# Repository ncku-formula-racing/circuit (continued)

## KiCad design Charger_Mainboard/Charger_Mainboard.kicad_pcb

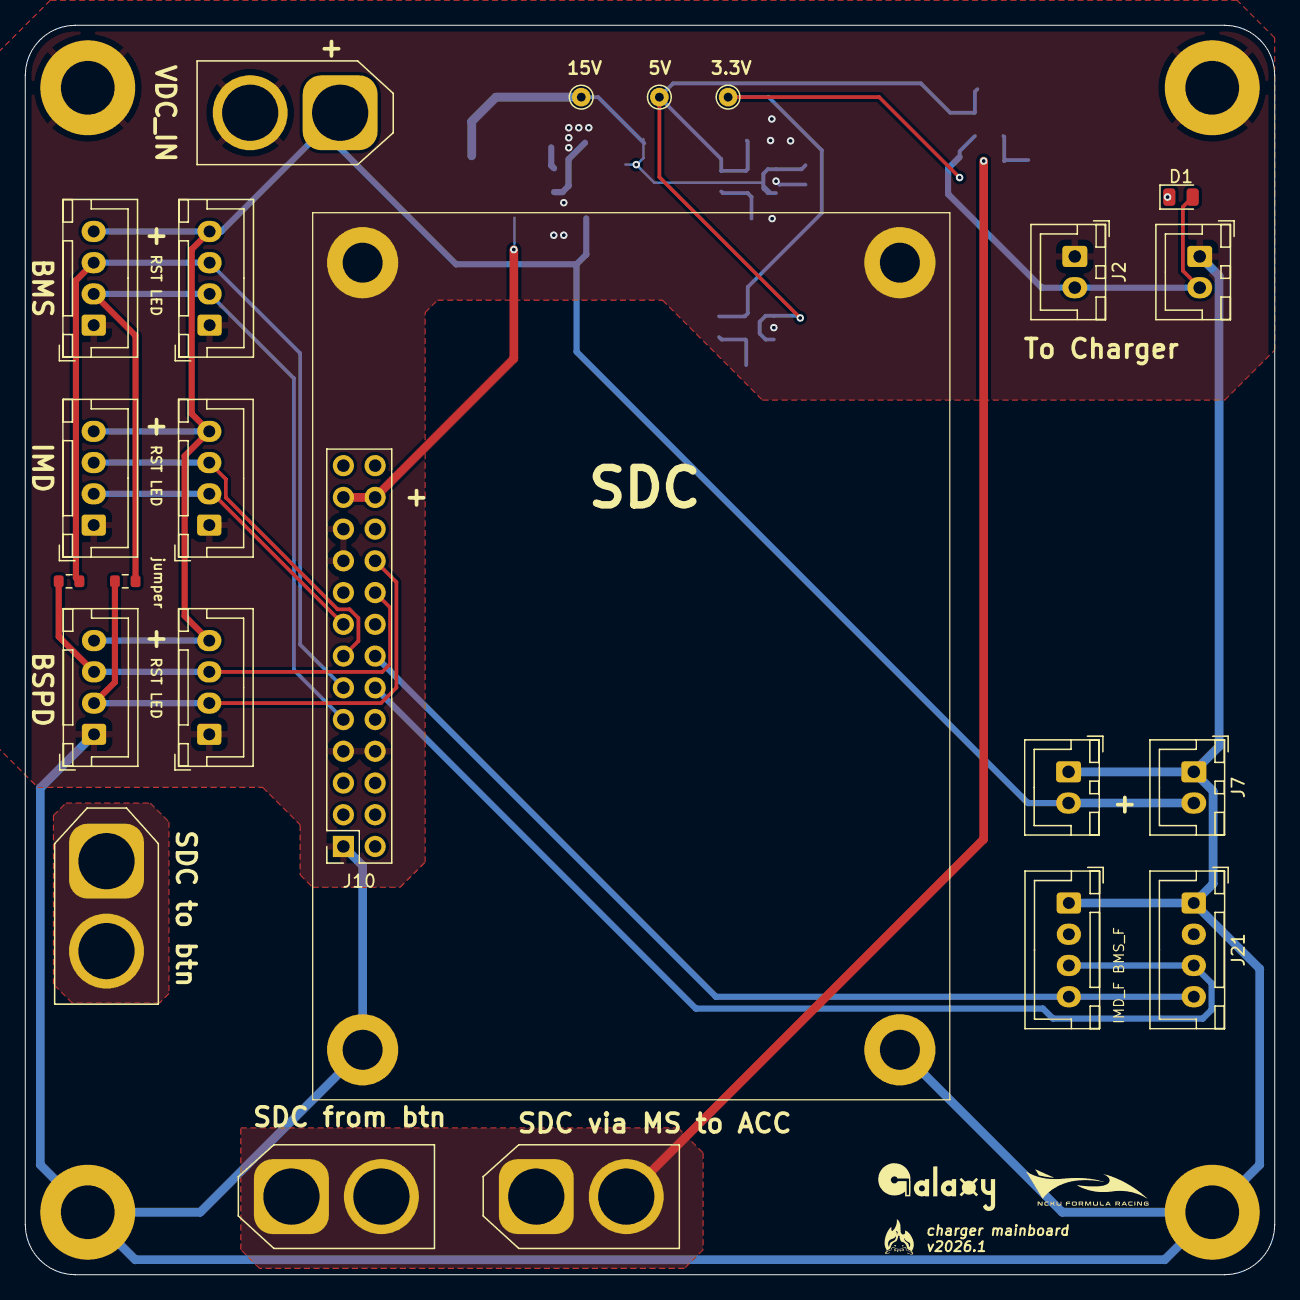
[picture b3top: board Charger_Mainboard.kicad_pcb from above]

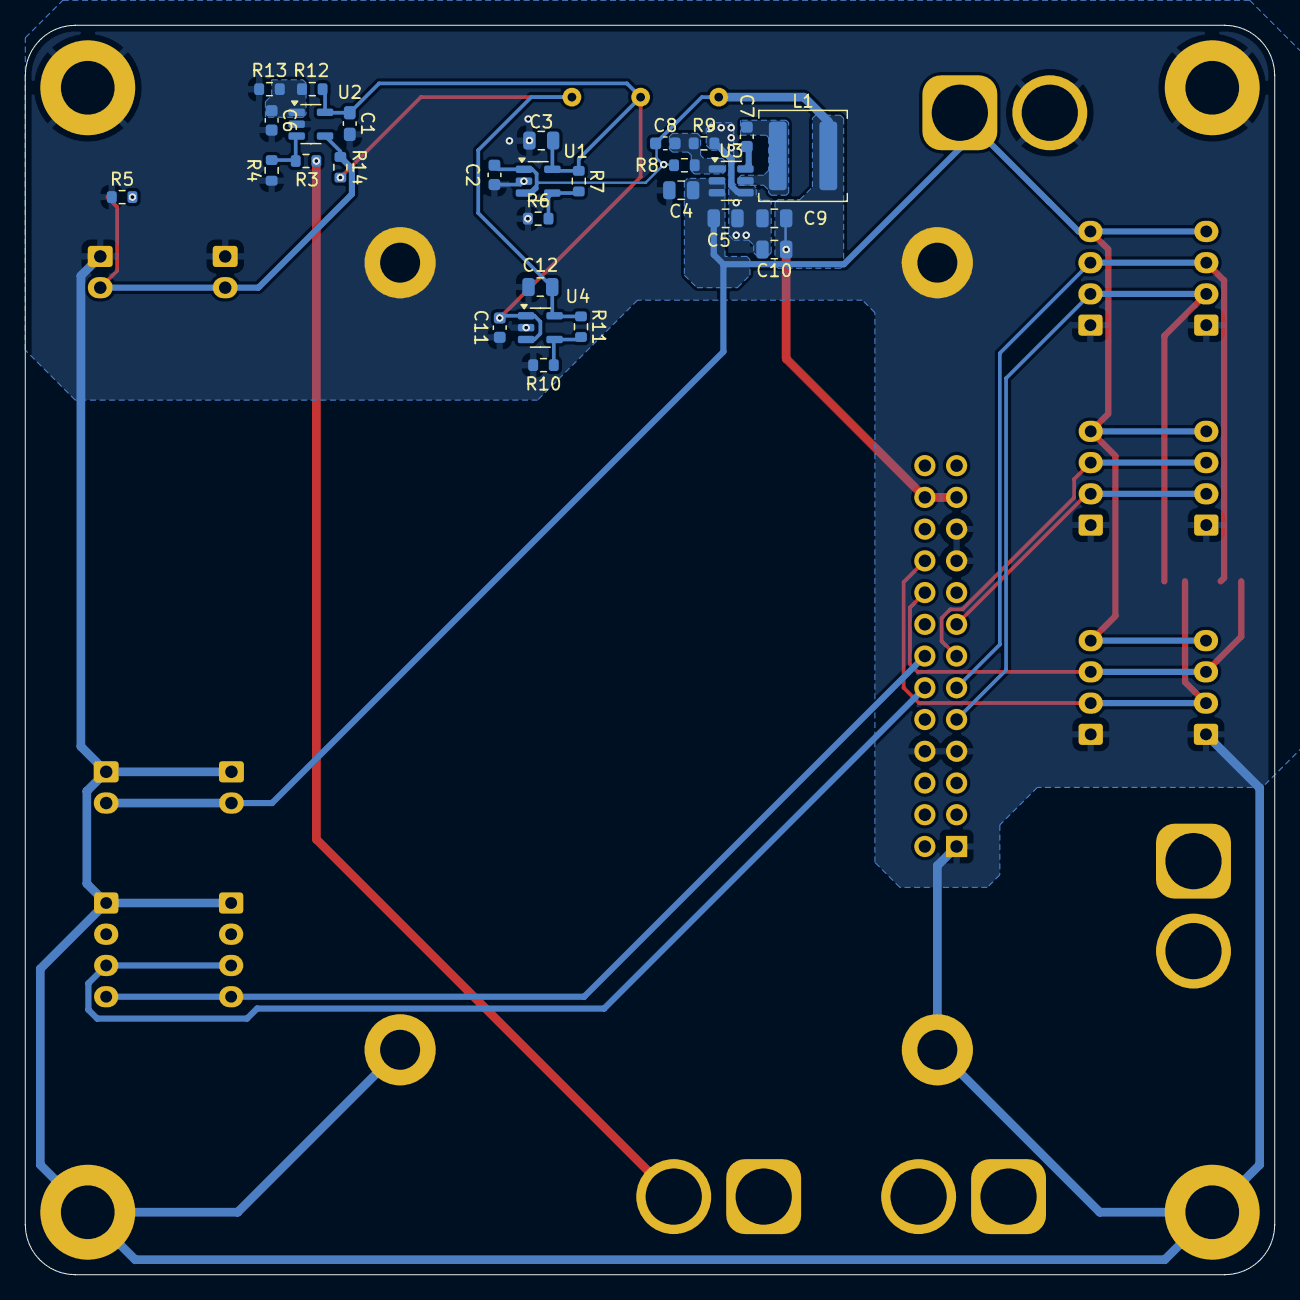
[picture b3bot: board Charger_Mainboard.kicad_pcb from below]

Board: 2 copper layers, 100.0 x 100.0 mm, 60 parts (29 on the bottom side), 24 nets.

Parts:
C1: 1u; C_0603_1608Metric_Pad1.08x0.95mm_HandSolder
C2, C11: 1u; C_0603_1608Metric
C3, C4, C5, C12: 10u; C_0805_2012Metric
C6, C7: 100n; C_0603_1608Metric
C8: 12p; C_0603_1608Metric
C9, C10: 22u; C_0805_2012Metric
D1: LED_Small; LED_0805_2012Metric
H1, H2#2, H3, H4#2: MountingHole_Pad; MountingHole_4.3mm_M4_ISO7380_Pad
H1#2, H2, H3#2, H4: MountingHole_Pad; MountingHole_3.2mm_M3_ISO7380_Pad
J1, J3, J4, J5: Conn_01x02; AMASS_XT60-M_1x02_P7.20mm_Vertical
J2, J2#2, J7, J7#2: Conn_01x02; JST_XH_B2B-XH-A_1x02_P2.50mm_Vertical
J8, J8#2, J18, J18#2, J21, J21#2, J22, J22#2: Conn_01x04; JST_XH_B4B-XH-A_1x04_P2.50mm_Vertical
J10: Conn_02x13_Odd_Even; PinSocket_2x13_P2.54mm_Vertical
L1: 15uH; L_Coilcraft_XAL6060-XXX
R1, R2: 0; R_0603_1608Metric
R3, R7: 301k; R_0603_1608Metric
R4, R6, R10: 100k; R_0603_1608Metric
R5, R12, R13: 10k; R_0603_1608Metric
R8: 534k; R_0603_1608Metric
R9: 30k1; R_0603_1608Metric
R11: 165k; R_0603_1608Metric
R14: 1k; R_0603_1608Metric
TP1, TP2, TP3: TestPoint; TestPoint_THTPad_D1.5mm_Drill0.7mm
U1, U4: AP2204K-ADJ; SOT-23-5
U2: AS331KTR-G1; SOT-23-5
U3: AP63200WU; TSOT-23-6

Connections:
+3V3: C12.1, R11.1, R14.1, TP3.1, U4.5 (VOUT)
+5V: C1.1, C3.1, C11.1, R7.1, R12.1, TP2.1, U1.5 (VOUT), U2.5, U4.1 (VIN), U4.3 (EN)
BMS_FAULT: J10.12, J21.3, J21#2.3
BMS_LED: J10.9, J22.2, J22#2.2, R2.1
BMS_RST: J10.11, J22.3, J22#2.3, R1.2
BSPD_LED: J8.2, J8#2.2, J10.20, R2.2
BSPD_RST: J8.3, J8#2.3, J10.18, R1.1
GND: C1.2, C2.2, C3.2, C4.2, C5.2, C6.2, C9.2, C10.2, C11.2, C12.2, H1.1, H1#2.1, H2.1, H2#2.1, H3.1, H3#2.1, H4.1, H4#2.1, J1.2, J2.1, J2#2.1, J7.1, J7#2.1, J8.1, J8#2.1, J10.1, J10.7, J10.8, J10.19, J10.21, J18.1, J18#2.1, J21.1, J21#2.1, J22.1, J22#2.1, R4.1, R5.1, R6.1, R9.2, R10.1, R13.2, U1.2 (GND), U2.2, U3.4 (GND), U4.2 (GND)
IMD_FAULT: J10.14, J21.4, J21#2.4
IMD_LED: J10.15, J18.2, J18#2.2
IMD_RST: J10.13, J18.3, J18#2.3
unnamed: D1.1 (K), R5.2
unnamed: R6.2, R7.2, U1.4 (ADJ)
unnamed: R3.1, R4.2, U2.3 (+)
unnamed: C6.1, R12.2, R13.1, U2.1 (-)
unnamed: C7.2, U3.6 (BST)
unnamed: C8.2, R8.2, R9.1, U3.1 (FB)
unnamed: C7.1, L1.1, U3.5 (SW)
unnamed: R10.2, R11.2, U4.4 (ADJ)
SDC_FROM_SDBUTTON: J4.1, J4.2, J5.1, J5.2, R3.2
SDC_IN: C2.1, C8.1, C9.1, C10.1, J10.23, J10.24, L1.2, R8.1, TP1.1, U1.1 (VIN), U1.3 (EN)
SDC_TO_SDBUTTON: J3.1, J3.2
VDC: C4.1, C5.1, J1.1, J7.2, J7#2.2, J8.4, J8#2.4, J18.4, J18#2.4, J22.4, J22#2.4, U3.2 (EN), U3.3 (IN)
charger_analog: D1.2 (A), J2.2, J2#2.2, R14.2, U2.4

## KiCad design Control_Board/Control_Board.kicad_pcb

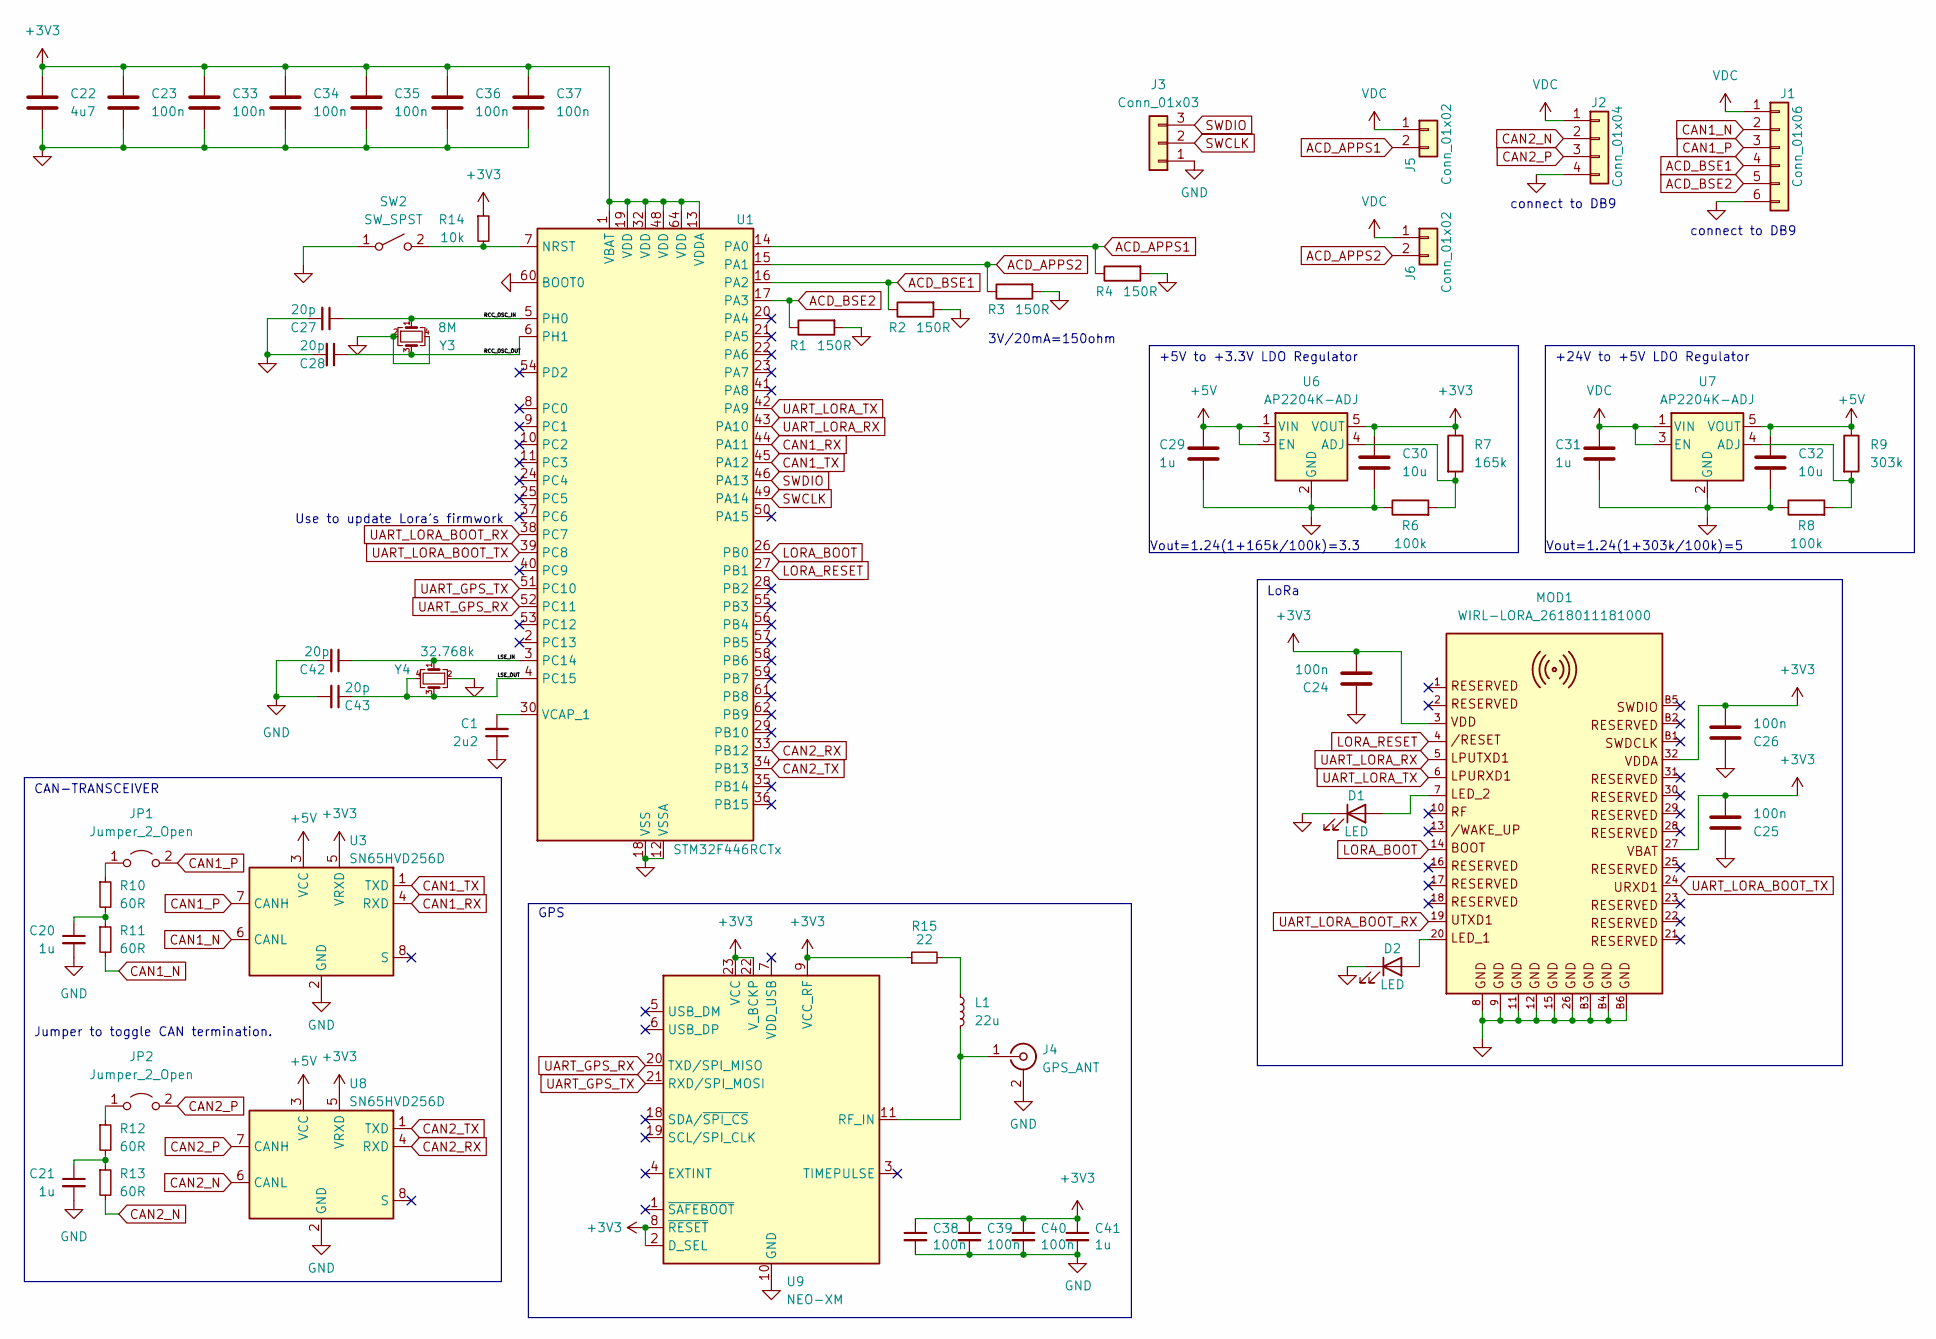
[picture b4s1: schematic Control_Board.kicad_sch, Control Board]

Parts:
C1: 2u2; C_0805_2012Metric
C20, C21, C29, C31, C41: 1u; C_0603_1608Metric
C22: 4u7; C_0805_2012Metric
C23, C24, C25, C26, C33, C34, C35, C36, C37, C38, C39, C40: 100n; C_0603_1608Metric
C27, C28, C42, C43: 20p; C_0603_1608Metric
C30, C32: 10u; C_0805_2012Metric
D1, D2: LED; LED_0805_2012Metric
J1: Conn_01x06; JST_XH_B6B-XH-A_1x06_P2.50mm_Vertical
J2: Conn_01x04; JST_XH_B4B-XH-A_1x04_P2.50mm_Vertical
J3: Conn_01x03; PinHeader_1x03_P2.54mm_Vertical
J4: GPS_ANT; U.FL_Hirose_U.FL-R-SMT-1_Vertical
J5, J6: Conn_01x02; JST_XH_B2B-XH-A_1x02_P2.50mm_Vertical
JP1, JP2: Jumper_2_Open; Jumper_P2.54mm_D0.7mm
L1: 22u; L_0805_2012Metric
MOD1: WIRL-LORA_2618011181000; WE-FP-8
R1, R2, R3, R4: 150R; R_0603_1608Metric
R6, R8: 100k; R_0603_1608Metric
R7: 165k; R_0603_1608Metric
R9: 303k; R_0603_1608Metric
R10, R11, R12, R13: 60R; R_0603_1608Metric
R14: 10k; R_0603_1608Metric
R15: 22; R_0603_1608Metric
SW2: SW_SPST; SW_SPST_FSMSM
U1: STM32F446RCTx; LQFP-64_10x10mm_P0.5mm
U3, U8: SN65HVD256D; SOIC-8_3.9x4.9mm_P1.27mm
U6, U7: AP2204K-ADJ; SOT-23-5
U9: NEO-XM; ublox_NEO
Y3: 8M; Crystal_SMD_SeikoEpson_FA238-4Pin_3.2x2.5mm
Y4: 32.768k; Crystal_SMD_SeikoEpson_FA238-4Pin_3.2x2.5mm

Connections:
+3V3: C22.1, C23.1, C24.2, C25.2, C26.2, C30.1, C33.1, C34.1, C35.1, C36.1, C37.1, C38.1, C39.1, C40.1, C41.1, MOD1.3, MOD1.27, MOD1.32, R7.1, R14.1, R15.1, U1.1 (VBAT), U1.13 (VDDA), U1.19 (VDD), U1.32 (VDD), U1.48 (VDD), U1.64 (VDD), U3.5 (VRXD), U6.5 (VOUT), U8.5 (VRXD), U9.2 (D_SEL), U9.8 (~RESET), U9.9 (VCC_RF), U9.22 (V_BCKP), U9.23 (VCC)
+5V: C29.1, C32.1, R9.1, U3.3 (VCC), U6.1 (VIN), U6.3 (EN), U7.5 (VOUT), U8.3 (VCC)
/LSE_IN: C42.1, U1.3 (PC14), Y4.1
/LSE_OUT: C43.1, U1.4 (PC15), Y4.3, Y4.4
/RCC_OSC_IN: C27.1, U1.5 (PH0), Y3.1
/RCC_OSC_OUT: C28.1, U1.6 (PH1), Y3.3
ACD_APPS1: J5.2, R4.1, U1.14 (PA0)
ACD_APPS2: J6.2, R3.1, U1.15 (PA1)
ACD_BSE1: J1.4, R2.1, U1.16 (PA2)
ACD_BSE2: J1.5, R1.1, U1.17 (PA3)
CAN1_N: J1.2, R11.2, U3.6 (CANL)
CAN1_P: J1.3, JP1.2 (B), U3.7 (CANH)
CAN1_RX: U1.44 (PA11), U3.4 (RXD)
CAN1_TX: U1.45 (PA12), U3.1 (TXD)
CAN2_N: J2.2, R13.2, U8.6 (CANL)
CAN2_P: J2.3, JP2.2 (B), U8.7 (CANH)
CAN2_RX: U1.33 (PB12), U8.4 (RXD)
CAN2_TX: U1.34 (PB13), U8.1 (TXD)
GND: C1.1, C20.2, C21.2, C22.2, C23.2, C24.1, C25.1, C26.1, C27.2, C28.2, C29.2, C30.2, C31.2, C32.2, C33.2, C34.2, C35.2, C36.2, C37.2, C38.2, C39.2, C40.2, C41.2, C42.2, C43.2, D1.1 (K), D2.1 (K), J1.6, J2.4, J3.1, J4.2 (Ext), MOD1.8, MOD1.9, MOD1.11, MOD1.12, MOD1.15, MOD1.26, MOD1.B3, MOD1.B4, MOD1.B6, R1.2, R2.2, R3.2, R4.2, R6.1, R8.1, SW2.1 (A), U1.12 (VSSA), U1.18 (VSS), U1.31 (VSS), U1.47 (VSS), U1.60 (BOOT0), U1.63 (VSS), U3.2 (GND), U6.2 (GND), U7.2 (GND), U8.2 (GND), U9.10 (GND), U9.12 (GND), U9.13 (GND), U9.24 (GND), Y3.2, Y3.4, Y4.2
LORA_BOOT: MOD1.14, U1.26 (PB0)
LORA_RESET: MOD1.4, U1.27 (PB1)
unnamed: C20.1, R10.2, R11.1
unnamed: C21.1, R12.2, R13.1
unnamed: D1.2 (A), MOD1.7
unnamed: D2.2 (A), MOD1.20
unnamed: J4.1 (In), L1.2, U9.11 (RF_IN)
unnamed: JP1.1 (A), R10.1
unnamed: JP2.1 (A), R12.1
unnamed: L1.1, R15.2
unnamed: R14.2, SW2.2 (B), U1.7 (NRST)
unnamed: C1.2, U1.30 (VCAP_1)
unnamed: R6.2, R7.2, U6.4 (ADJ)
unnamed: R8.2, R9.2, U7.4 (ADJ)
SWCLK: J3.2, U1.49 (PA14)
SWDIO: J3.3, U1.46 (PA13)
UART_GPS_RX: U1.52 (PC11), U9.20 (TXD/SPI_MISO)
UART_GPS_TX: U1.51 (PC10), U9.21 (RXD/SPI_MOSI)
UART_LORA_BOOT_RX: MOD1.19, U1.38 (PC7)
UART_LORA_BOOT_TX: MOD1.24, U1.39 (PC8)
UART_LORA_RX: MOD1.5, U1.43 (PA10)
UART_LORA_TX: MOD1.6, U1.42 (PA9)
VDC: C31.1, J1.1, J2.1, J5.1, J6.1, U7.1 (VIN), U7.3 (EN)

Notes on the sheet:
Vout=1.24(1+165k/100k)=3.3
connect to DB9
Jumper to toggle CAN termination.
CAN-TRANSCEIVER
Vout=1.24(1+303k/100k)=5
3V/20mA=150ohm
GPS
Use to update Lora's firmwork
+24V to +5V LDO Regulator
+5V to +3.3V LDO Regulator
LoRa

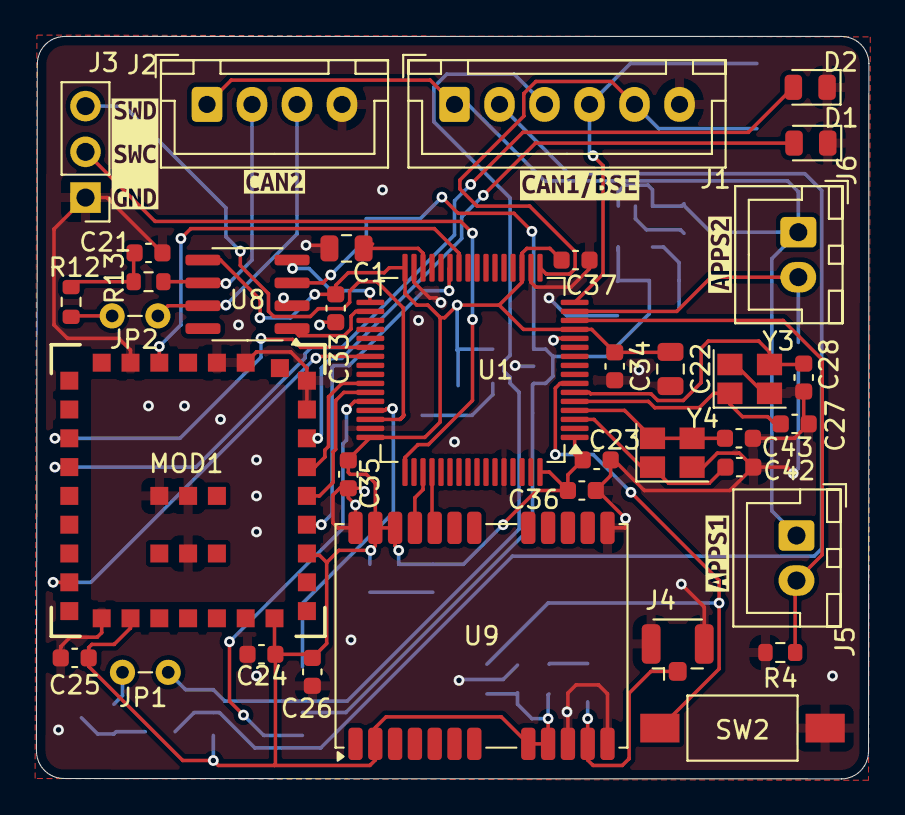
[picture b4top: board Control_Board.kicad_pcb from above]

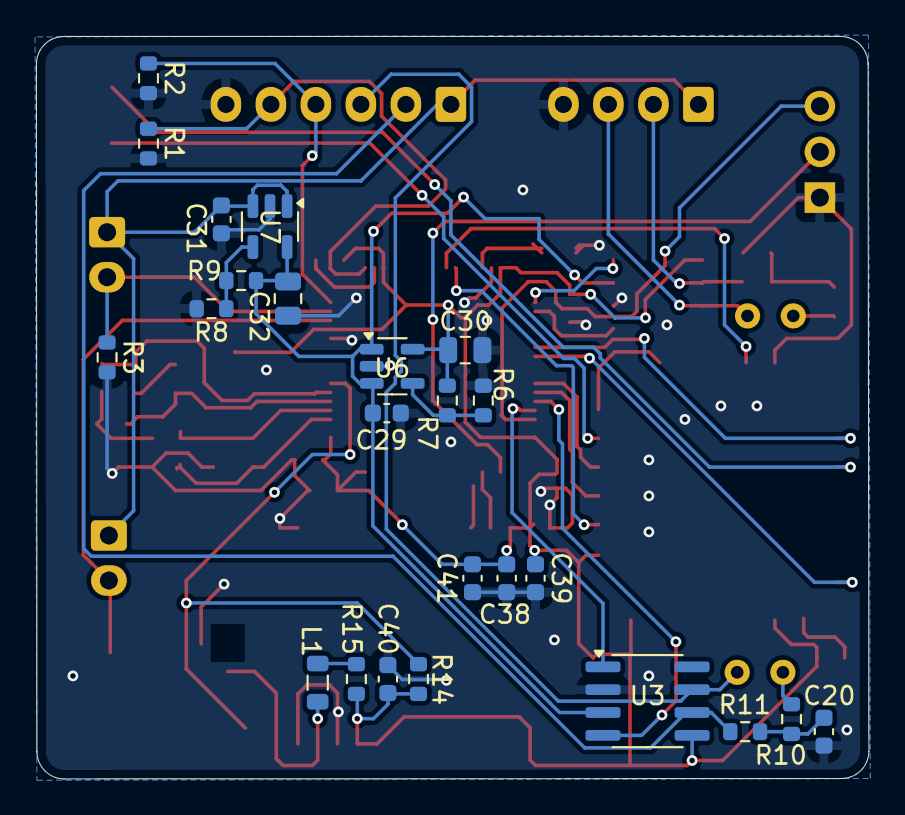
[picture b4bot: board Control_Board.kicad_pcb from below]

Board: 2 copper layers, 46.3 x 41.3 mm, 65 parts (24 on the bottom side), 42 nets.

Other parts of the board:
kibuzzard-68852EE2: G***; kibuzzard-68852EE2
kibuzzard-68852F9B: G***; kibuzzard-68852F9B
kibuzzard-68852FF1: G***; kibuzzard-68852FF1
kibuzzard-68853119: G***; kibuzzard-68853119
kibuzzard-68853151: G***; kibuzzard-68853151

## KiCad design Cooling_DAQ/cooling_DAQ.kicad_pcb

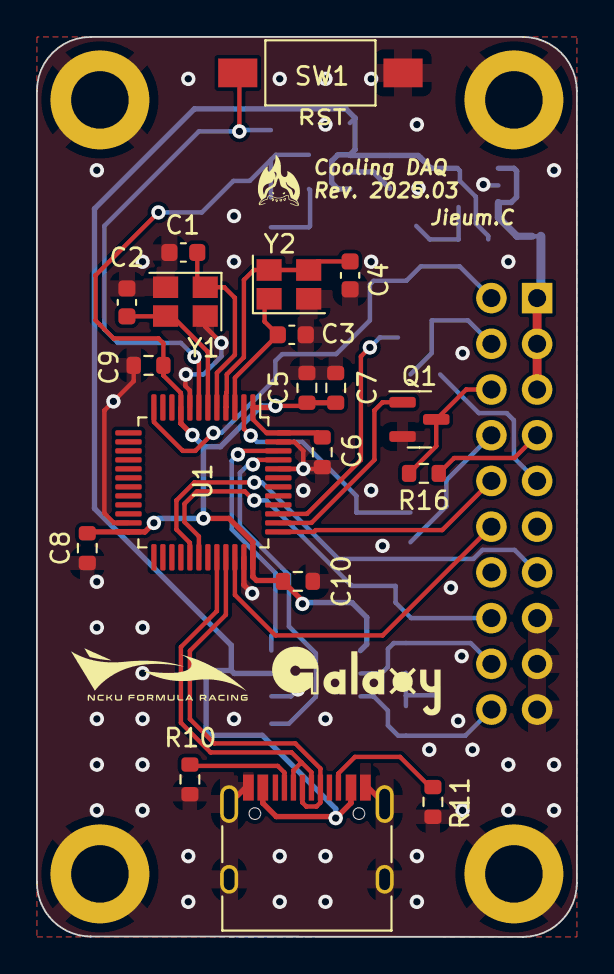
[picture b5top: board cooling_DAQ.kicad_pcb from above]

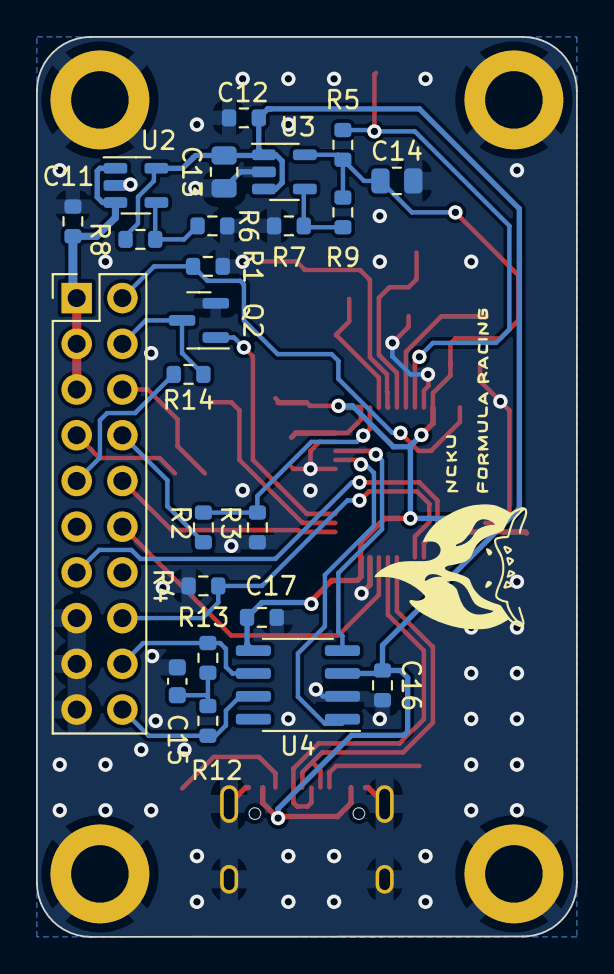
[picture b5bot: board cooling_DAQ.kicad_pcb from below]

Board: 2 copper layers, 30.0 x 50.0 mm, 47 parts (24 on the bottom side), 33 nets.

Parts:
C1, C2, C3, C4: 20p; C_0603_1608Metric
C5, C6, C8, C9, C10, C16, C17: 100n; R_0603_1608Metric
C7, C11, C12: 1u; R_0603_1608Metric
C13, C14: 10u; R_0805_2012Metric
C15: 1u; C_0603_1608Metric
H1, H2, H3, H4: MountingHole_Pad; MountingHole_3.2mm_M3_ISO14580_Pad
J1: Conn_02x10_Odd_Even; PinHeader_2x10_P2.54mm_Vertical
J7: USB_C_Receptacle_USB2.0_16P; USB_C_Receptacle_HRO_TYPE-C-31-M-12
Q1, Q2: 2N7002; SOT-23
R1, R4: 4.7k; R_0603_1608Metric
R2: 47k; R_0603_1608Metric
R3, R6, R7: 100k; R_0603_1608Metric
R5, R14, R16: 10k; R_0603_1608Metric
R8: 301k; R_0603_1608Metric
R9: 165k; R_0603_1608Metric
R10, R11: 5k1; R_0603_1608Metric
R12, R13: 60R; R_0603_1608Metric
SW1: SW_SPST; SW_SPST_FSMSM
U1: STM32F103C8Tx; LQFP-48_7x7mm_P0.5mm
U2, U3: AP2204K-ADJ; SOT-23-5
U4: SN65HVD256D; SOIC-8_3.9x4.9mm_P1.27mm
Y1: 8M; Crystal_SMD_SeikoEpson_FA238-4Pin_3.2x2.5mm
Y2: 32.768k; Crystal_SMD_SeikoEpson_FA238-4Pin_3.2x2.5mm

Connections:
+3V3: C5.1, C6.1, C7.1, C8.1, C9.1, C10.1, C14.1, C17.1, R5.1, R9.1, U1.1 (VBAT), U1.9 (VDDA), U1.24 (VDD), U1.36 (VDD), U1.48 (VDD), U3.5 (VOUT), U4.5 (VRXD)
+5V: C12.1, C13.1, C16.1, J7.A4 (VBUS), J7.A9 (VBUS), J7.B4 (VBUS), J7.B9 (VBUS), R8.1, U2.5 (VOUT), U3.1 (VIN), U3.3 (EN), U4.3 (VCC)
/LSE_IN: C3.1, U1.3 (PC14), Y2.1
/LSE_OUT: C4.1, U1.4 (PC15), Y2.3, Y2.4
/RCC_OSC_IN: C1.1, U1.5 (PD0), Y1.1
/RCC_OSC_OUT: C2.1, U1.6 (PD1), Y1.3
ADC_CH1: R2.2, R3.1, U1.2 (PC13)
CAN+: J1.20, R12.1, U4.7 (CANH)
CAN-: J1.18, R13.2, U4.6 (CANL)
CAN_RX: U1.46 (PB9), U4.4 (RXD)
CAN_TX: U1.45 (PB8), U4.1 (TXD)
FAN_PWM: J1.4, Q2.3 (D), R14.1
FAN_PWR: J1.9, R14.2
GND: C1.2, C2.2, C3.2, C4.2, C5.2, C6.2, C7.2, C8.2, C9.2, C10.2, C11.2, C12.2, C13.2, C14.2, C15.2, C16.2, C17.2, H1.1, H2.1, H3.1, H4.1, J1.15, J1.17, J1.19, J7.A1 (GND), J7.A12 (GND), J7.B1 (GND), J7.B12 (GND), J7.S1 (SHIELD), Q1.2 (S), Q2.2 (S), R1.2, R3.2, R4.2, R6.1, R7.1, R10.2, R11.2, SW1.1 (A), U1.8 (VSSA), U1.23 (VSS), U1.35 (VSS), U1.44 (BOOT0), U1.47 (VSS), U2.2 (GND), U3.2 (GND), U4.2 (GND), Y1.2, Y1.4, Y2.2
unnamed: C15.1, R12.2, R13.1
unnamed: J7.A5 (CC1), R10.1
unnamed: J7.B5 (CC2), R11.1
unnamed: R5.2, SW1.2 (B), U1.7 (NRST)
unnamed: R6.2, R8.2, U2.4 (ADJ)
unnamed: R7.2, R9.2, U3.4 (ADJ)
PT_signal: J1.8, R2.1
PUMP_PWM: J1.6, Q1.3 (D), R16.1
PUMP_PWR: J1.7, R16.2
PWM_OUT: Q1.1 (G), U1.38 (PA15)
PWM_OUT_2: Q2.1 (G), U1.39 (PB3)
SYS_JTCK-SWCLK: J1.10, U1.37 (PA14)
SYS_JTMS-SWDIO: J1.12, U1.34 (PA13)
TIM1_CH1: J1.13, U1.29 (PA8)
USART1: J1.16, R4.1, U1.30 (PA9)
USART2: J1.2, R1.1, U1.12 (PA2)
USB_D+: J7.A6 (D+), J7.B6 (D+), U1.33 (PA12)
USB_D-: J7.A7 (D-), J7.B7 (D-), U1.32 (PA11)
VDC: C11.1, J1.1, J1.3, J1.5, U2.1 (VIN), U2.3 (EN)

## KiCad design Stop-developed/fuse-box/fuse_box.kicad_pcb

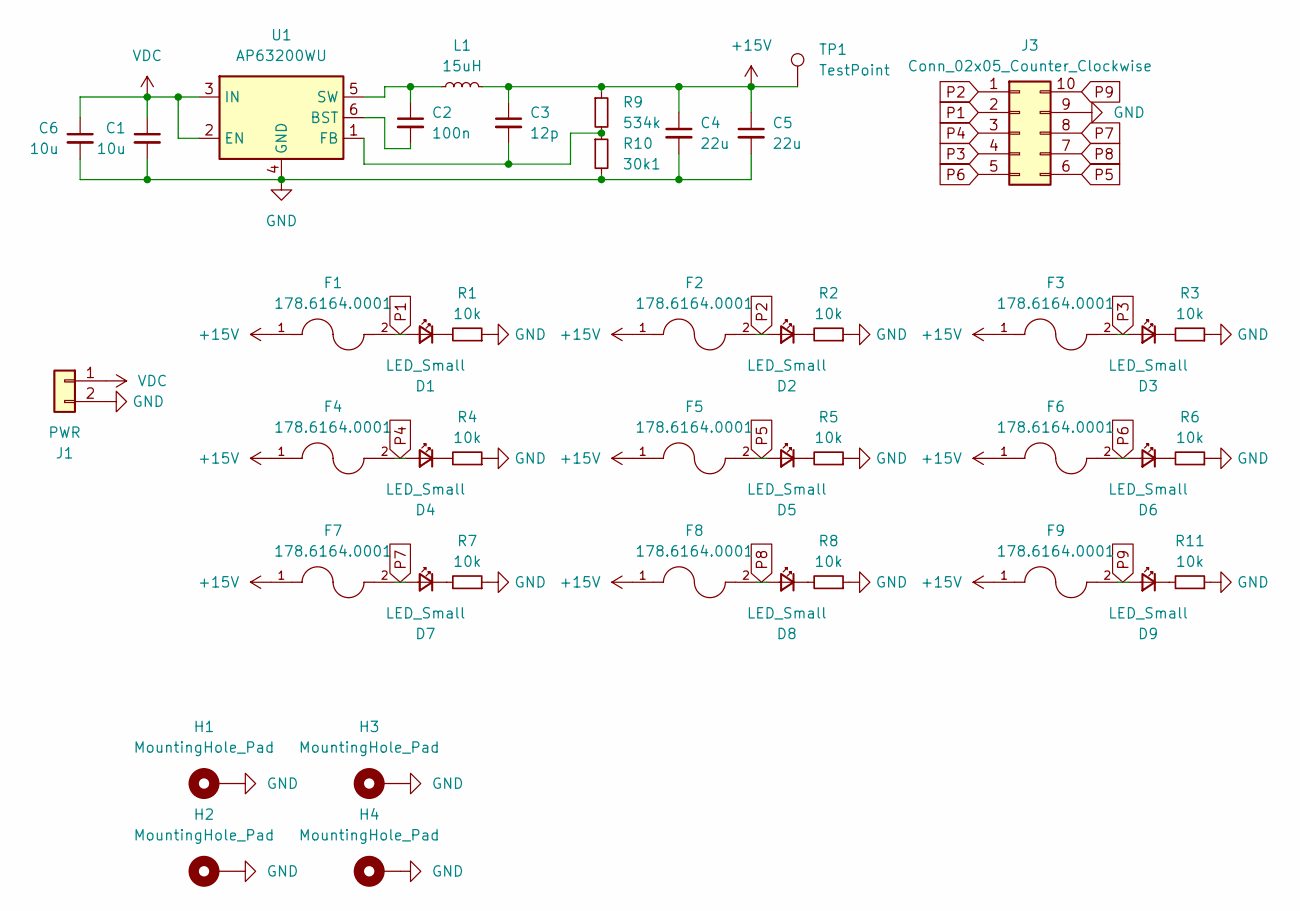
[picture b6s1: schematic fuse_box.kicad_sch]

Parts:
C1, C6: 10u; C_0805_2012Metric
C2: 100n; C_0603_1608Metric
C3: 12p; C_0603_1608Metric
C4, C5: 22u; C_0805_2012Metric
D1, D2, D3, D4, D5, D6, D7, D8, D9: LED_Small; LED_0805_2012Metric
F1, F2, F3, F4, F5, F6, F7, F8, F9: 178.6164.0001; LITTELFUSE_178.6164.0001; PARTREV 06.04.05
H1, H2, H3, H4: MountingHole_Pad; MountingHole_3.2mm_M3_ISO7380_Pad
J1: PWR; AMASS_XT60-M_1x02_P7.20mm_Vertical
J3: Conn_02x05_Counter_Clockwise; PinHeader_2x05_P2.54mm_Vertical
L1: 15uH; L_Coilcraft_XAL6060-XXX
R1, R2, R3, R4, R5, R6, R7, R8, R11: 10k; R_0603_1608Metric
R9: 534k; R_0603_1608Metric
R10: 30k1; R_0603_1608Metric
TP1: TestPoint; TestPoint_THTPad_D1.5mm_Drill0.7mm
U1: AP63200WU; TSOT-23-6

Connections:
+15V: C3.1, C4.1, C5.1, F1.1, F2.1, F3.1, F4.1, F5.1, F6.1, F7.1, F8.1, F9.1, L1.2, R9.1, TP1.1
GND: C1.2, C4.2, C5.2, C6.2, H1.1, H2.1, H3.1, H4.1, J1.2, J3.9, R1.1, R2.1, R3.1, R4.1, R5.1, R6.1, R7.1, R8.1, R10.2, R11.1, U1.4 (GND)
unnamed: D1.1 (K), R1.2
unnamed: D2.1 (K), R2.2
unnamed: D3.1 (K), R3.2
unnamed: D4.1 (K), R4.2
unnamed: D5.1 (K), R5.2
unnamed: D6.1 (K), R6.2
unnamed: D7.1 (K), R7.2
unnamed: D8.1 (K), R8.2
unnamed: D9.1 (K), R11.2
unnamed: C2.2, U1.6 (BST)
unnamed: C3.2, R9.2, R10.1, U1.1 (FB)
unnamed: C2.1, L1.1, U1.5 (SW)
P1: D1.2 (A), F1.2, J3.2
P2: D2.2 (A), F2.2, J3.1
P3: D3.2 (A), F3.2, J3.4
P4: D4.2 (A), F4.2, J3.3
P5: D5.2 (A), F5.2, J3.6
P6: D6.2 (A), F6.2, J3.5
P7: D7.2 (A), F7.2, J3.8
P8: D8.2 (A), F8.2, J3.7
P9: D9.2 (A), F9.2, J3.10
VDC: C1.1, C6.1, J1.1, U1.2 (EN), U1.3 (IN)

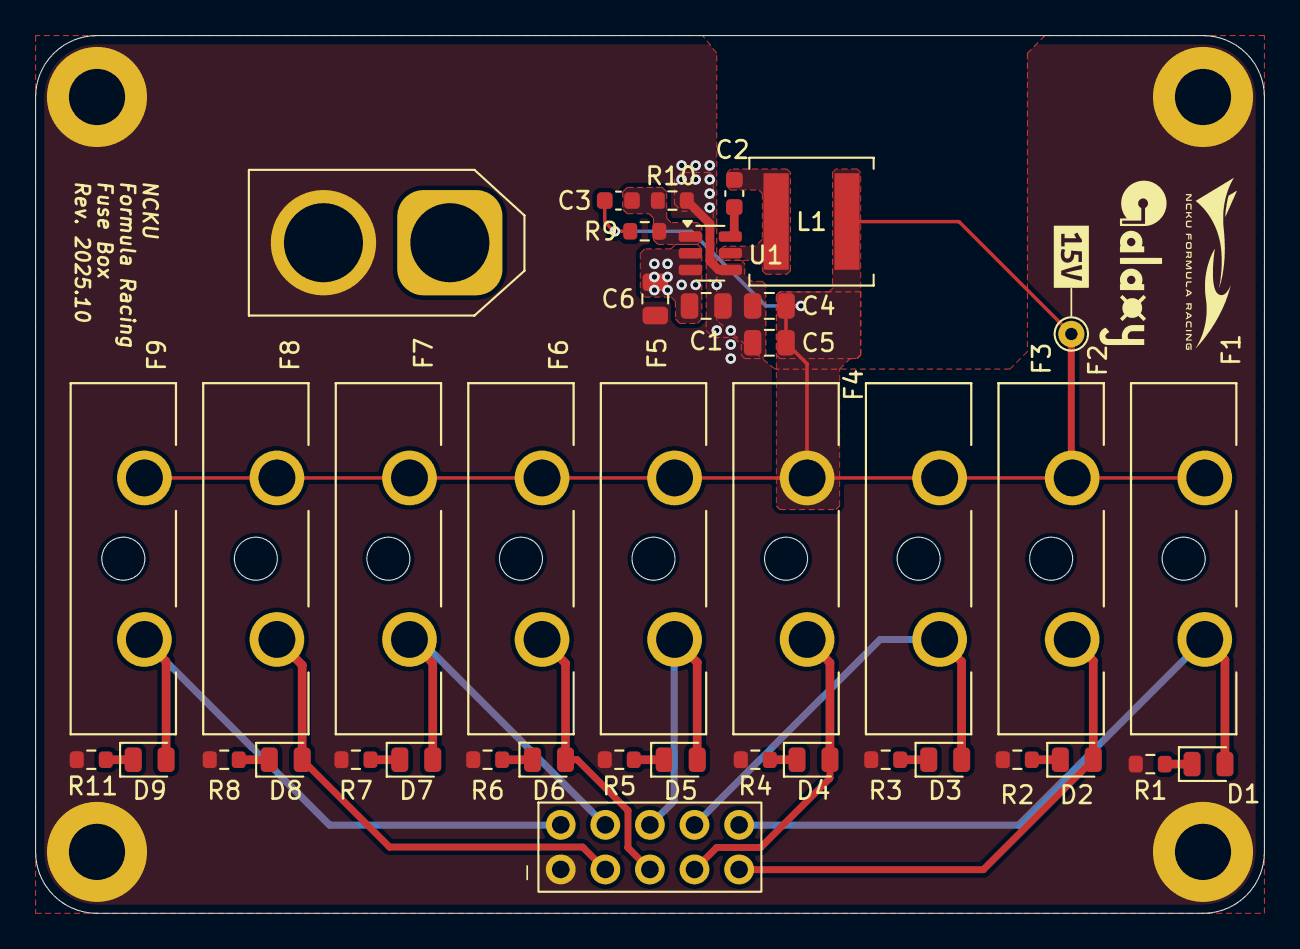
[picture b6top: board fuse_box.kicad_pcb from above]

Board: 2 copper layers, 70.0 x 50.0 mm, 45 parts (1 on the bottom side), 24 nets.

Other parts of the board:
kibuzzard-67D51968: G***; kibuzzard-67D51968

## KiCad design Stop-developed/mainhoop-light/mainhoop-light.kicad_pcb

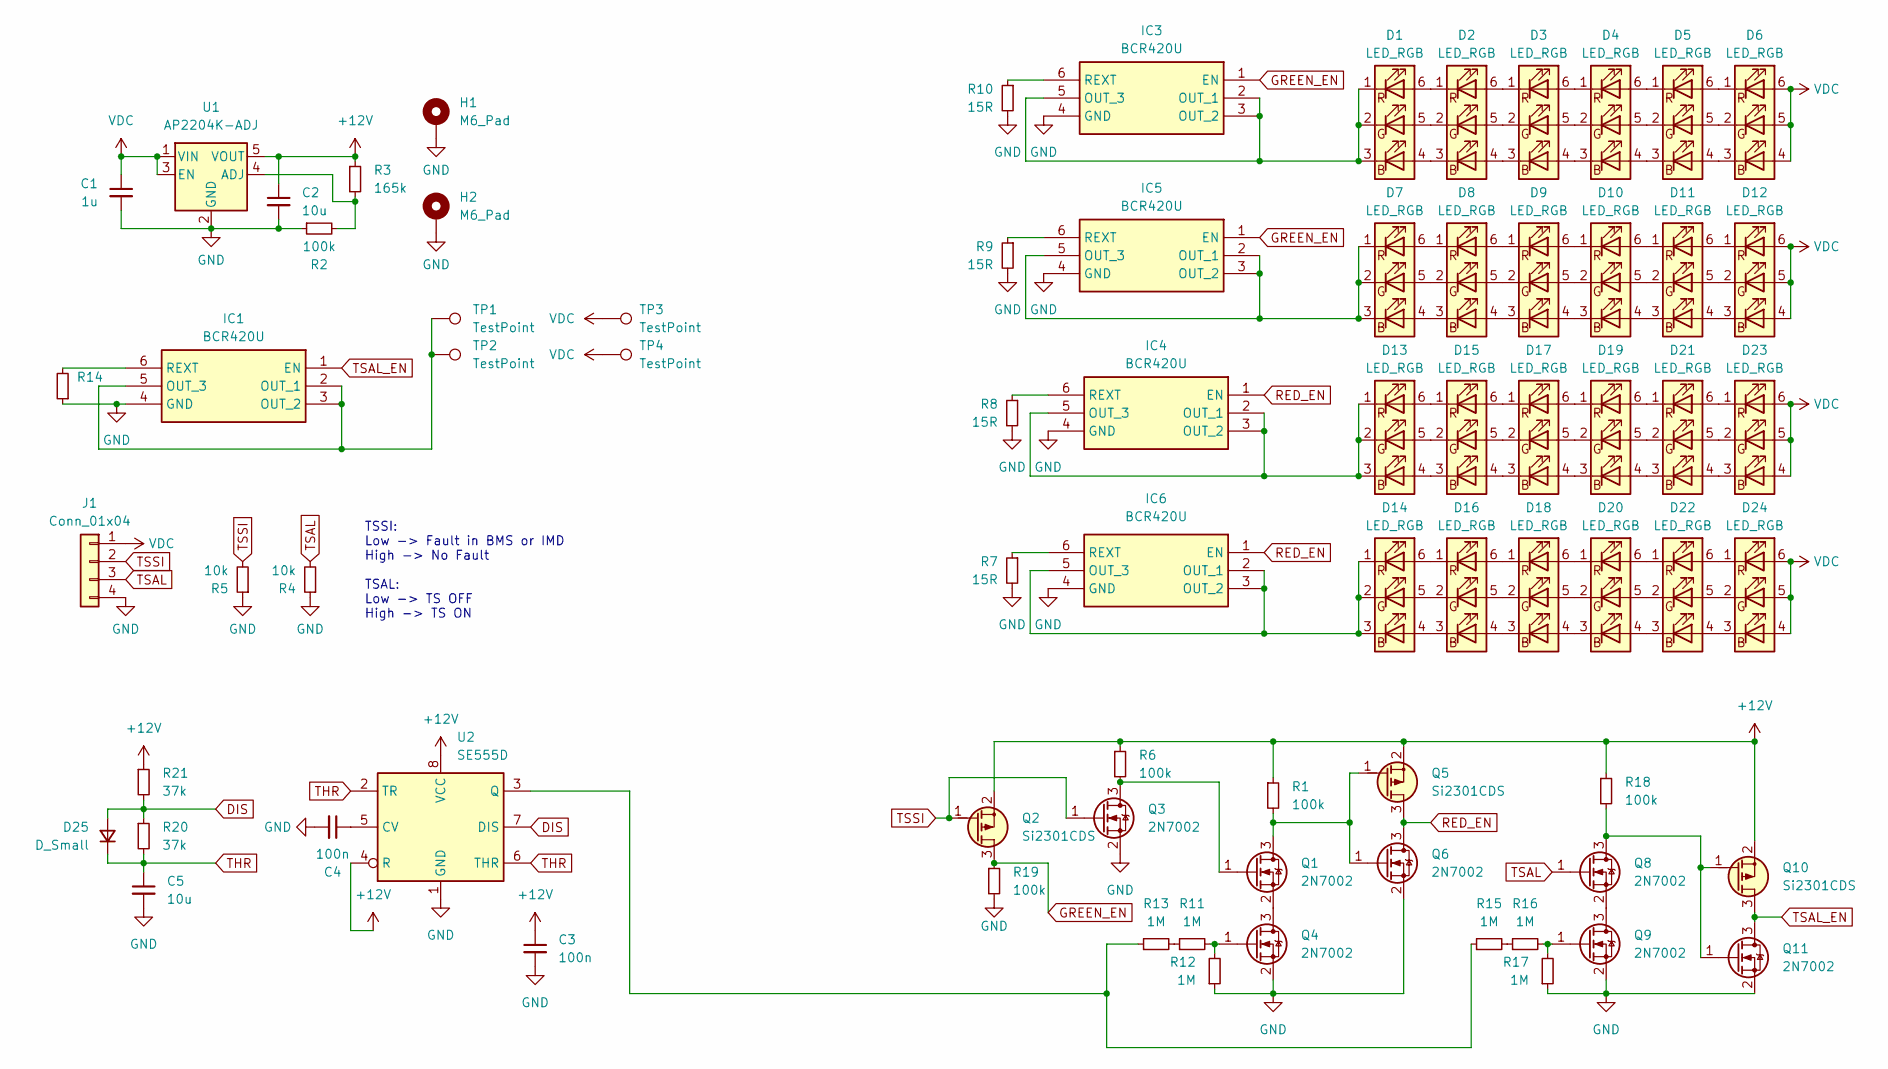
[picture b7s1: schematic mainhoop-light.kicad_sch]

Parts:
C1: 1u; C_0603_1608Metric
C2, C5: 10u; C_0805_2012Metric
C3, C4: 100n; C_0603_1608Metric
D1, D2, D3, D4, D5, D6, D7, D8, D9, D10, D11, D12, D13, D14, D15, D16, D17, D18, D19, D20, D21, D22, D23, D24: LED_RGB; LED_RGB_5050-6
D25: D_Small; D_SOD-123F
H1, H2: M6_Pad; MountingHole_6.4mm_M6_DIN965_Pad_TopBottom
IC1, IC3, IC4, IC5, IC6: BCR420U; SOT-23-6; Mouser Part Number 621-BCR420UW6-7
J1: Conn_01x04; Wuerth_WR-WTB_64800411622_1x04_P1.50mm_Vertical
Q1, Q3, Q4, Q6, Q8, Q9, Q11: 2N7002; SOT-23
Q2, Q5, Q10: Si2301CDS; SOT-23
R1, R2, R6, R18, R19: 100k; R_0603_1608Metric
R3: 165k; R_0603_1608Metric
R4, R5: 10k; R_0603_1608Metric
R7, R8, R9, R10: 15R; R_0603_1608Metric
R11, R12, R13, R15, R16, R17: 1M; R_0603_1608Metric
R14: R_0603_1608Metric
R20, R21: 37k; R_0603_1608Metric
TP1, TP2, TP3, TP4: TestPoint; Pin_D1.3mm_L11.0mm
U1: AP2204K-ADJ; SOT-23-5
U2: SE555D; SOIC-8_3.9x4.9mm_P1.27mm

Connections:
+12V: C2.1, C3.1, Q2.2 (S), Q5.2 (S), Q10.2 (S), R1.1, R3.1, R6.1, R18.1, R21.1, U1.5 (VOUT), U2.4 (R), U2.8 (VCC)
DIS: D25.2 (A), R20.1, R21.2, U2.7 (DIS)
GND: C1.2, C2.2, C3.2, C4.2, C5.2, H1.1, H2.1, IC1.4 (GND), IC3.4 (GND), IC4.4 (GND), IC5.4 (GND), IC6.4 (GND), J1.4, Q3.2 (S), Q4.2 (S), Q6.2 (S), Q9.2 (S), Q11.2 (S), R2.1, R4.1, R5.1, R7.2, R8.2, R9.2, R10.2, R12.1, R14.1, R17.1, R19.2, U1.2 (GND), U2.1 (GND)
GREEN_EN: IC3.1 (EN), IC5.1 (EN), Q2.3 (D), R19.1
unnamed: D1.4 (BA), D2.3 (BK)
unnamed: D1.1 (RK), D1.2 (GK), D1.3 (BK), IC3.2 (OUT_1), IC3.3 (OUT_2), IC3.5 (OUT_3)
unnamed: D1.5 (GA), D2.2 (GK)
unnamed: D1.6 (RA), D2.1 (RK)
unnamed: D2.4 (BA), D3.3 (BK)
unnamed: D2.5 (GA), D3.2 (GK)
unnamed: D2.6 (RA), D3.1 (RK)
unnamed: D3.4 (BA), D4.3 (BK)
unnamed: D3.5 (GA), D4.2 (GK)
unnamed: D3.6 (RA), D4.1 (RK)
unnamed: D4.4 (BA), D5.3 (BK)
unnamed: D4.5 (GA), D5.2 (GK)
unnamed: D4.6 (RA), D5.1 (RK)
unnamed: D5.4 (BA), D6.3 (BK)
unnamed: D5.5 (GA), D6.2 (GK)
unnamed: D5.6 (RA), D6.1 (RK)
unnamed: D7.4 (BA), D8.3 (BK)
unnamed: D7.1 (RK), D7.2 (GK), D7.3 (BK), IC5.2 (OUT_1), IC5.3 (OUT_2), IC5.5 (OUT_3)
unnamed: D7.5 (GA), D8.2 (GK)
unnamed: D7.6 (RA), D8.1 (RK)
unnamed: D8.4 (BA), D9.3 (BK)
unnamed: D8.5 (GA), D9.2 (GK)
unnamed: D8.6 (RA), D9.1 (RK)
unnamed: D10.4 (BA), D11.3 (BK)
unnamed: D9.4 (BA), D10.3 (BK)
unnamed: D10.5 (GA), D11.2 (GK)
unnamed: D9.5 (GA), D10.2 (GK)
unnamed: D10.6 (RA), D11.1 (RK)
unnamed: D9.6 (RA), D10.1 (RK)
unnamed: D11.4 (BA), D12.3 (BK)
unnamed: D11.5 (GA), D12.2 (GK)
unnamed: D11.6 (RA), D12.1 (RK)
unnamed: D13.4 (BA), D15.3 (BK)
unnamed: D13.1 (RK), D13.2 (GK), D13.3 (BK), IC4.2 (OUT_1), IC4.3 (OUT_2), IC4.5 (OUT_3)
unnamed: D13.5 (GA), D15.2 (GK)
unnamed: D13.6 (RA), D15.1 (RK)
unnamed: D14.4 (BA), D16.3 (BK)
unnamed: D14.1 (RK), D14.2 (GK), D14.3 (BK), IC6.2 (OUT_1), IC6.3 (OUT_2), IC6.5 (OUT_3)
unnamed: D14.5 (GA), D16.2 (GK)
unnamed: D14.6 (RA), D16.1 (RK)
unnamed: D15.4 (BA), D17.3 (BK)
unnamed: D15.5 (GA), D17.2 (GK)
unnamed: D15.6 (RA), D17.1 (RK)
unnamed: D16.4 (BA), D18.3 (BK)
unnamed: D16.5 (GA), D18.2 (GK)
unnamed: D16.6 (RA), D18.1 (RK)
unnamed: D17.4 (BA), D19.3 (BK)
unnamed: D17.5 (GA), D19.2 (GK)
unnamed: D17.6 (RA), D19.1 (RK)
unnamed: D18.4 (BA), D20.3 (BK)
unnamed: D18.5 (GA), D20.2 (GK)
unnamed: D18.6 (RA), D20.1 (RK)
unnamed: D19.4 (BA), D21.3 (BK)
unnamed: D19.5 (GA), D21.2 (GK)
unnamed: D19.6 (RA), D21.1 (RK)
unnamed: D20.4 (BA), D22.3 (BK)
unnamed: D20.5 (GA), D22.2 (GK)
unnamed: D20.6 (RA), D22.1 (RK)
unnamed: D21.4 (BA), D23.3 (BK)
unnamed: D21.5 (GA), D23.2 (GK)
unnamed: D21.6 (RA), D23.1 (RK)
unnamed: D22.4 (BA), D24.3 (BK)
unnamed: D22.5 (GA), D24.2 (GK)
unnamed: D22.6 (RA), D24.1 (RK)
unnamed: IC1.2 (OUT_1), IC1.3 (OUT_2), IC1.5 (OUT_3), TP1.1, TP2.1
unnamed: IC1.6 (REXT), R14.2
unnamed: IC3.6 (REXT), R10.1
unnamed: IC4.6 (REXT), R8.1
unnamed: IC5.6 (REXT), R9.1
unnamed: IC6.6 (REXT), R7.1
unnamed: Q1.3 (D), Q5.1 (G), Q6.1 (G), R1.2
unnamed: Q1.1 (G), Q3.3 (D), R6.2
unnamed: Q1.2 (S), Q4.3 (D)
unnamed: Q4.1 (G), R11.2, R12.2
unnamed: Q8.2 (S), Q9.3 (D)
unnamed: Q9.1 (G), R16.2, R17.2
unnamed: Q8.3 (D), Q10.1 (G), Q11.1 (G), R18.2
unnamed: R11.1, R13.2
unnamed: R15.2, R16.1
unnamed: R2.2, R3.2, U1.4 (ADJ)
unnamed: C4.1, U2.5 (CV)
unnamed: R13.1, R15.1, U2.3 (Q)
RED_EN: IC4.1 (EN), IC6.1 (EN), Q5.3 (D), Q6.3 (D)
THR: C5.1, D25.1 (K), R20.2, U2.2 (TR), U2.6 (THR)
TSAL: J1.3, Q8.1 (G), R4.2
TSAL_EN: IC1.1 (EN), Q10.3 (D), Q11.3 (D)
TSSI: J1.2, Q2.1 (G), Q3.1 (G), R5.2
VDC: C1.1, D6.4 (BA), D6.5 (GA), D6.6 (RA), D12.4 (BA), D12.5 (GA), D12.6 (RA), D23.4 (BA), D23.5 (GA), D23.6 (RA), D24.4 (BA), D24.5 (GA), D24.6 (RA), J1.1, TP3.1, TP4.1, U1.1 (VIN), U1.3 (EN)

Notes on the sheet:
TSSI: Low -> Fault in BMS or IMD High -> No Fault TSAL: Low -> TS OFF High -> TS ON
